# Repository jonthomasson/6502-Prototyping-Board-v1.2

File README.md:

# 6502-Prototyping-Board-v1.2

![enter image description here](https://lh3.googleusercontent.com/dqhXyFna1i5g64ReIDbXhT_9_lCE78yEcwSUMLsjWN7HjGM4Np-Uf1zc_w4Khi1hd384zVwSwuUfOBHs40V_MTYlUP_jXGLSV8Q2ezvhHs5ocKfKs3LgeXCJLcW2rBHjo85IMTgyBdq8A81JBiFT8mXPGY9lxDYMvT_1gU5DdgI0zk7k6rLz-5Nj7pmCWX47QRDXbrKZOrh9HyB9loaVLAzCwFxsja-6bSkUOXlZ4JcyZhOngb16zHO6qLTQVpIoA0lOMYQ7VOmICIMyuzwn9TpFFmqfktvgupSC1bdkxCwXLhD3MTZ9tw8PcTqfVld1-K3E99ZKjStddeI4ycGGY_wtz-mF8tkEFEu6p0RNVQz2mZtMQ8GfHHu-NU1xVhJXccq2QHNr6-MfTwD136gq-nS00Qe4NoIfeVMc5vifECh6nv2GEebfnq3P50OWNIqXPYWPc2J102FOA1mCoB2gjrx8k4-TqxiEFEhZ_x-zw7Rvp47dxKI4cks8961DUxog5FamGkD9sdlPeouvdK3RxzDPcEACU8scOdDyDG1Lsi2Q8YvIEtA6TWiZoxI1qN3QOq1IZr6gIIJc8EYJycQCqGh-oy19KnWR4njvcsz4=w1265-h949-no)

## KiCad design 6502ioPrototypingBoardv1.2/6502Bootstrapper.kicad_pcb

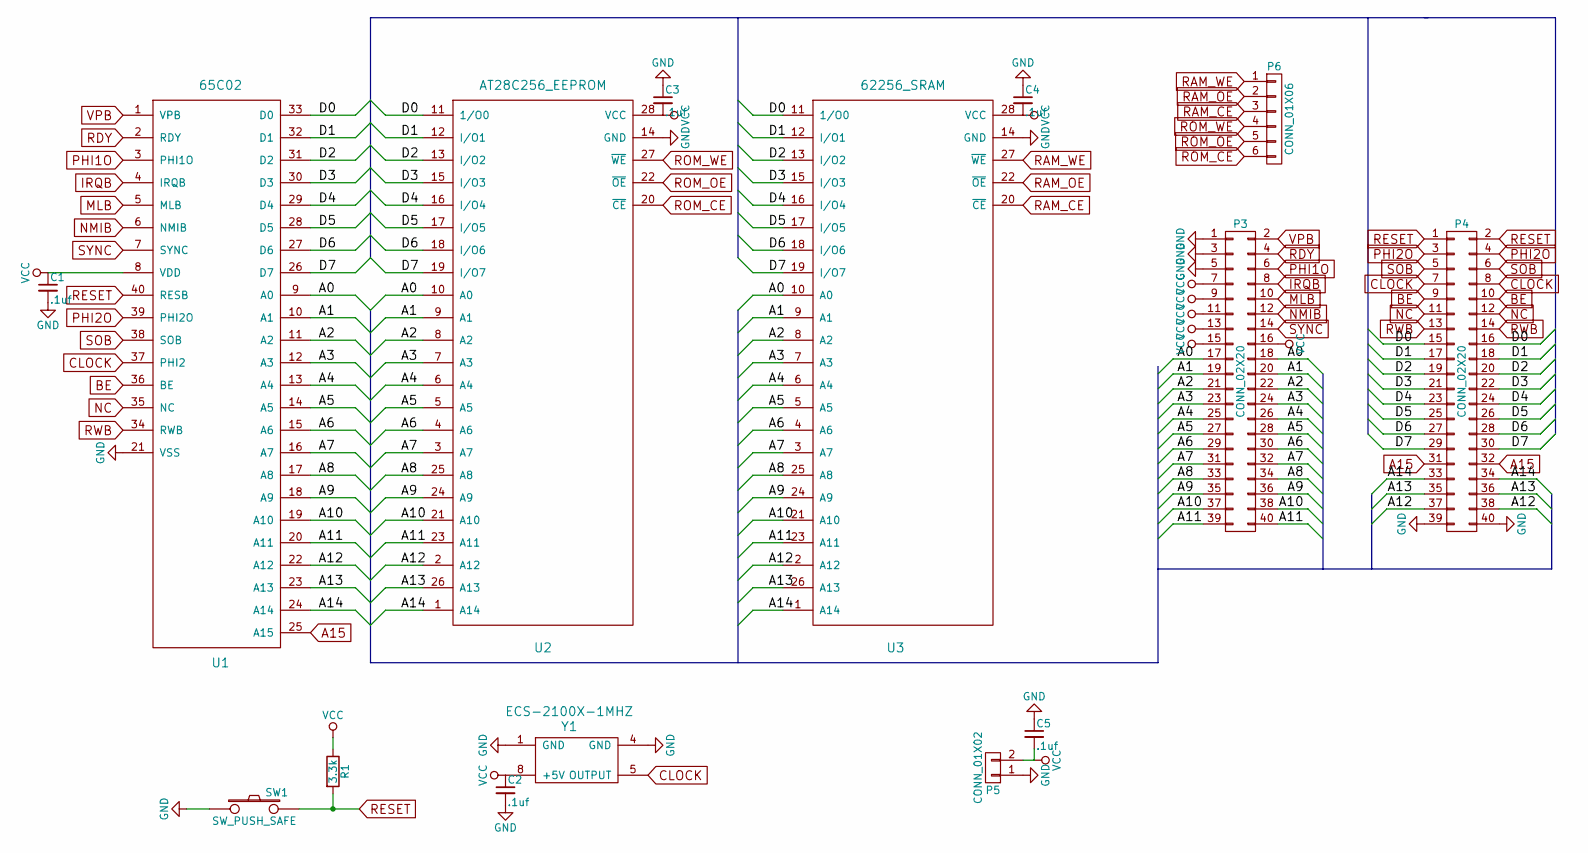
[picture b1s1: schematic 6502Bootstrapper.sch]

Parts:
C1, C2, C3, C4, C5: .1uf; C_Disc_D3_P2.5
P3, P4: CONN_02X20; Pin_Header_Straight_2x20
P5: CONN_01X02; Pin_Header_Straight_1x02
P6: CONN_01X06; Pin_Header_Straight_1x06
R1: 3.3k; Resistor_Horizontal_RM10mm
SW1: SW_PUSH_SAFE; TACTILE_SWITCH
U1: 65C02; 65c02
U2: AT28C256_EEPROM; A302_ND_SOCKET
U3: 62256_SRAM
Y1: ECS-2100X-1MHZ; ECS-2100AX

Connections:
/A0: P3.17, P3.18, U1.9 (A0), U2.10 (A0), U3.10 (A0)
/A1: P3.19, P3.20, U1.10 (A1), U2.9 (A1), U3.9 (A1)
/A2: P3.21, P3.22, U1.11 (A2), U2.8 (A2), U3.8 (A2)
/A3: P3.23, P3.24, U1.12 (A3), U2.7 (A3), U3.7 (A3)
/A4: P3.25, P3.26, U1.13 (A4), U2.6 (A4), U3.6 (A4)
/A5: P3.27, P3.28, U1.14 (A5), U2.5 (A5), U3.5 (A5)
/A6: P3.29, P3.30, U1.15 (A6), U2.4 (A6), U3.4 (A6)
/A7: P3.31, P3.32, U1.16 (A7), U2.3 (A7), U3.3 (A7)
/A8: P3.33, P3.34, U1.17 (A8), U2.25 (A8), U3.25 (A8)
/A9: P3.35, P3.36, U1.18 (A9), U2.24 (A9), U3.24 (A9)
/A10: P3.37, P3.38, U1.19 (A10), U2.21 (A10), U3.21 (A10)
/A11: P3.39, P3.40, U1.20 (A11), U2.23 (A11), U3.23 (A11)
/A12: P4.37, P4.38, U1.22 (A12), U2.2 (A12), U3.2 (A12)
/A13: P4.35, P4.36, U1.23 (A13), U2.26 (A13), U3.26 (A13)
/A14: P4.33, P4.34, U1.24 (A14), U2.1 (A14), U3.1 (A14)
/D0: P4.15, P4.16, U1.33 (D0), U2.11 (1/O0), U3.11 (1/O0)
/D1: P4.17, P4.18, U1.32 (D1), U2.12 (I/O1), U3.12 (I/O1)
/D2: P4.19, P4.20, U1.31 (D2), U2.13 (I/O2), U3.13 (I/O2)
/D3: P4.21, P4.22, U1.30 (D3), U2.15 (I/O3), U3.15 (I/O3)
/D4: P4.23, P4.24, U1.29 (D4), U2.16 (I/O4), U3.16 (I/O4)
/D5: P4.25, P4.26, U1.28 (D5), U2.17 (I/O5), U3.17 (I/O5)
/D6: P4.27, P4.28, U1.27 (D6), U2.18 (I/O6), U3.18 (I/O6)
/D7: P4.29, P4.30, U1.26 (D7), U2.19 (I/O7), U3.19 (I/O7)
A15: P4.31, P4.32, U1.25 (A15)
BE: P4.9, P4.10, U1.36 (BE)
CLOCK: P4.7, P4.8, U1.37 (PHI2), Y1.5 (OUTPUT)
GND: C1.2, C2.2, C3.1, C4.1, C5.1, P3.1, P3.3, P3.5, P4.39, P4.40, P5.1, SW1.1, U1.21 (VSS), U2.14 (GND), U3.14 (GND), Y1.1 (GND), Y1.4 (GND)
IRQB: P3.8, U1.4 (IRQB)
MLB: P3.10, U1.5 (MLB)
NC: P4.11, P4.12, U1.35 (NC)
NMIB: P3.12, U1.6 (NMIB)
PHI1O: P3.6, U1.3 (PHI1O)
PHI2O: P4.3, P4.4, U1.39 (PHI2O)
RAM_CE: P6.3, U3.20 (~CE)
RAM_OE: P6.2, U3.22 (~OE)
RAM_WE: P6.1, U3.27 (~WE)
RDY: P3.4, U1.2 (RDY)
RESET: P4.1, P4.2, R1.2, SW1.4, U1.40 (RESB)
ROM_CE: P6.6, U2.20 (~CE)
ROM_OE: P6.5, U2.22 (~OE)
ROM_WE: P6.4, U2.27 (~WE)
RWB: P4.13, P4.14, U1.34 (RWB)
SOB: P4.5, P4.6, U1.38 (SOB)
SYNC: P3.14, U1.7 (SYNC)
VCC: C1.1, C2.1, C3.2, C4.2, C5.2, P3.7, P3.9, P3.11, P3.13, P3.15, P3.16, P5.2, R1.1, U1.8 (VDD), U2.28 (VCC), U3.28 (VCC), Y1.8 (+5V)
VPB: P3.2, U1.1 (VPB)

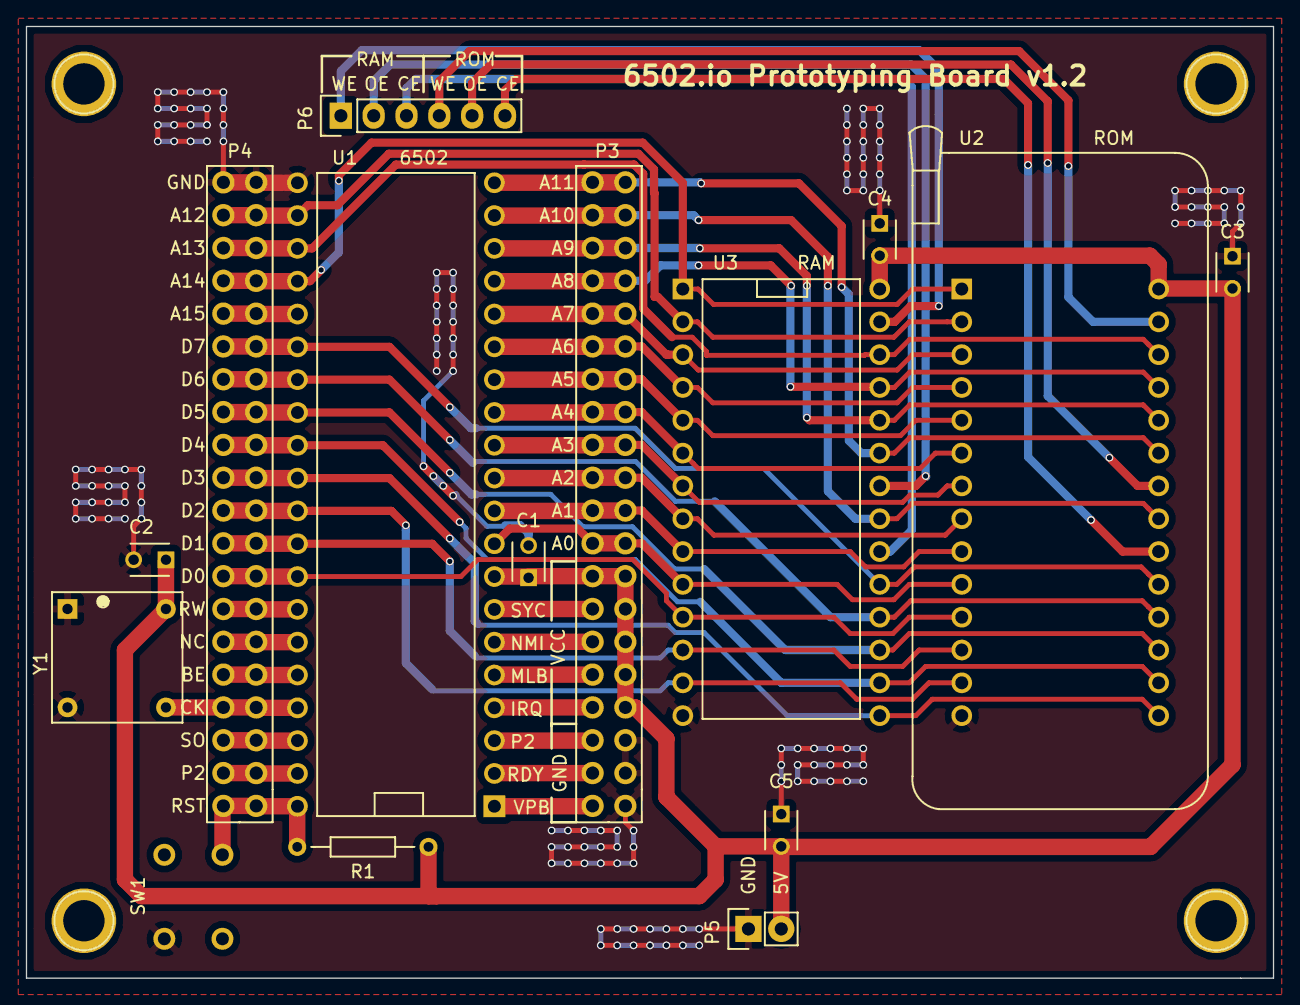
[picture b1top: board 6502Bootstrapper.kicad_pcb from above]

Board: 2 copper layers, 96.5 x 73.7 mm, 15 parts (0 on the bottom side), 46 nets.

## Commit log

2015-11-04 :tada: Added .gitattributes & .gitignore files
2017-04-19 syncing to master
2017-04-19 added raytraced pcb
